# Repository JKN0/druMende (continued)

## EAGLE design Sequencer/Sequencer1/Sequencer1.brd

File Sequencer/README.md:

# Sequencer

Sequencer is  divided to two circuit boards

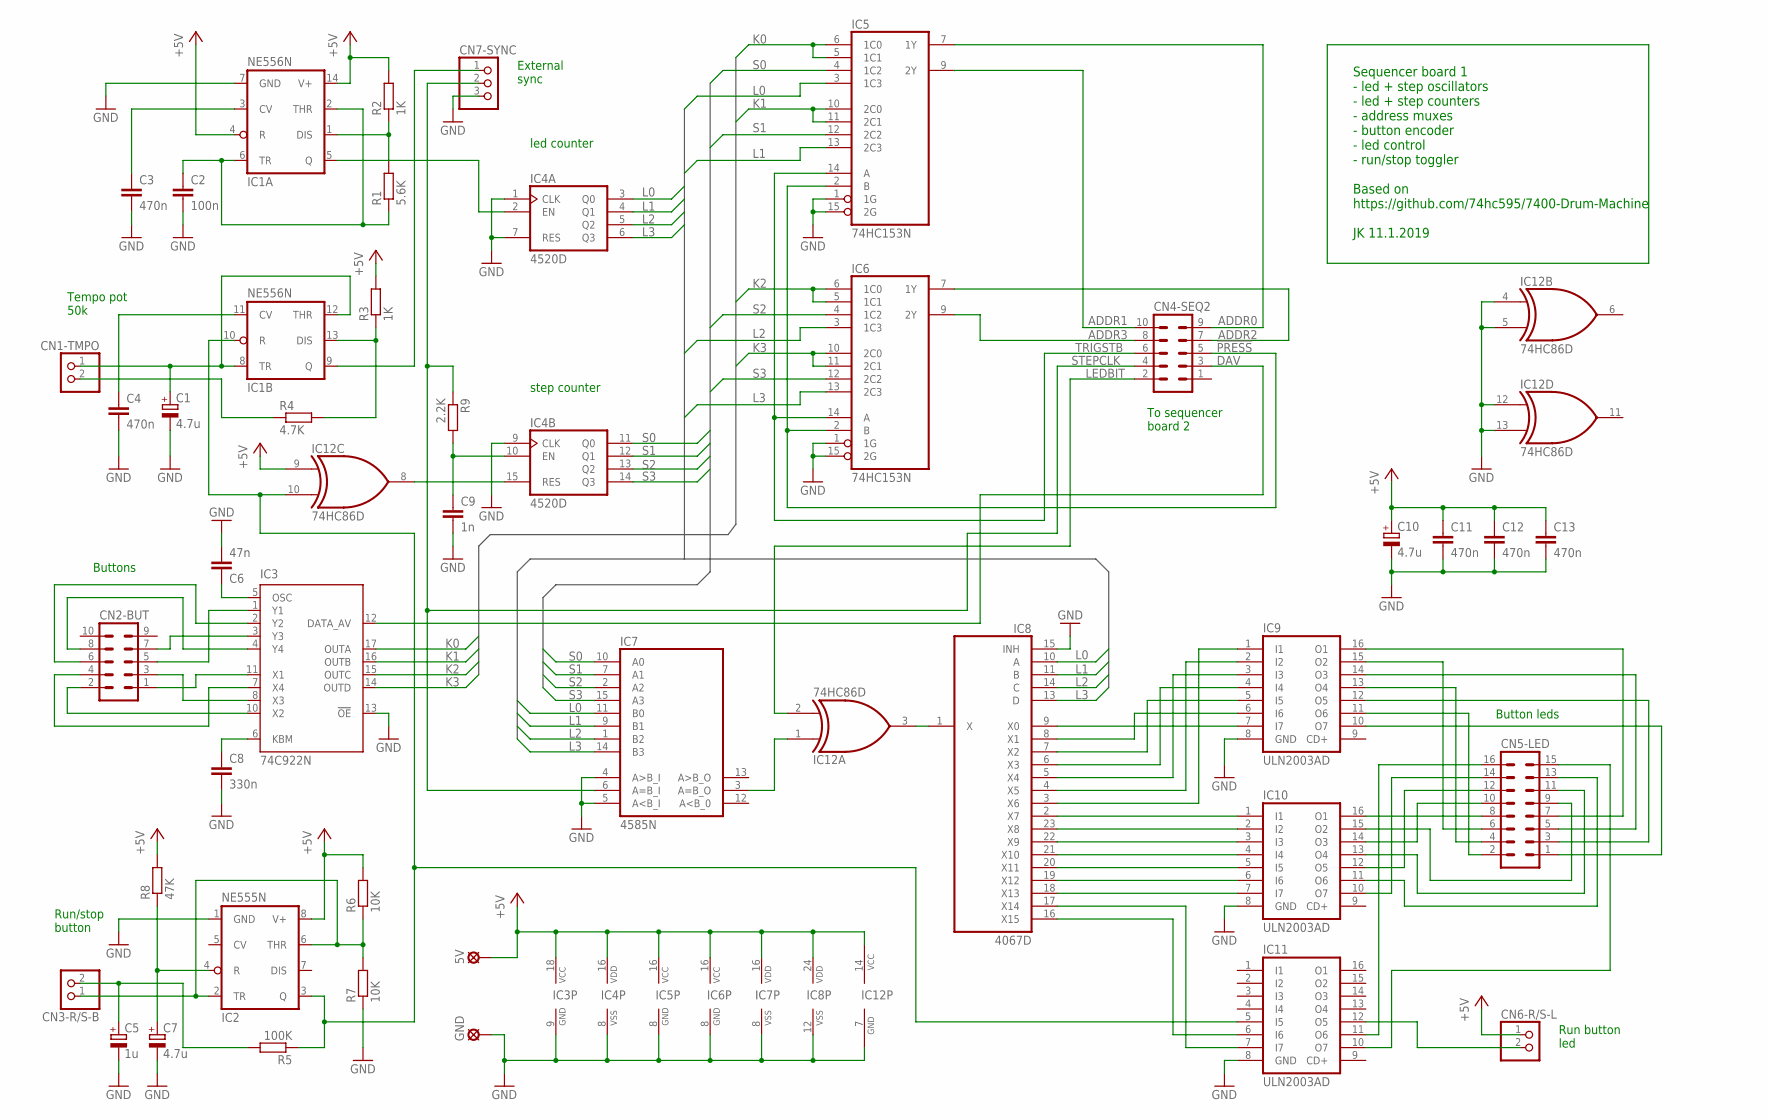
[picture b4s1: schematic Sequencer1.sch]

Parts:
5V: LSP10
C1, C7, C10: 4.7u; SMC_A
C2: 100n; C0805
C3, C4, C11, C12, C13: 470n; C0603
C5: 1u; SMC_A
C6: 47n; C0805
C8: 330n; C0805
C9: 1n; C0805
CN1-TMPO, CN3-R/S-B, CN6-R/S-L: PINHD-1X2; 1X02
CN2-BUT, CN4-SEQ2: MA05-2
CN5-LED: MA08-2
CN7-SYNC: PINHD-1X3; 1X03
GND: LSP10
IC1: NE556N; DIL14
IC2: NE555N; DIL08
IC3: 74C922N; DIL18
IC4: 4520D; SO16
IC5, IC6: 74HC153N; DIL16
IC7: 4585N; DIL16
IC8: 4067D; SO24W
IC9, IC10, IC11: ULN2003AD; SO16
IC12: 74HC86D; SO14
R1: 5.6K; R0805
R2, R3: 1K; R0805
R4: 4.7K; R0805
R5: 100K; R0805
R6, R7: 10K; R0805
R8: 47K; R0805
R9: 2.2K; R0805

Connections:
!PRESS: CN4-SEQ2.5, IC5.2 (B), IC6.2 (B)
!RUN: IC4.15 (RES), IC12.8 (O)
+5V: 5V.MP, C10.+, C11.1, C12.1, C13.1, CN6-R/S-L.1, IC1.4 (R), IC1.14 (V+), IC2.8 (V+), IC3.18 (VCC), IC4.16 (VDD), IC5.16 (VCC), IC6.16 (VCC), IC7.16 (VDD), IC8.24 (VDD), IC12.9 (I0), IC12.14 (VCC), R2.2, R3.2, R6.2, R8.2
ADDR0: CN4-SEQ2.9, IC5.7 (1Y)
ADDR1: CN4-SEQ2.10, IC5.9 (2Y)
ADDR2: CN4-SEQ2.7, IC6.7 (1Y)
ADDR3: CN4-SEQ2.8, IC6.9 (2Y)
DAV: CN4-SEQ2.3, IC3.12 (DATA_AV)
GND: C1.-, C2.2, C3.2, C4.2, C5.-, C6.2, C7.-, C8.2, C9.2, C10.-, C11.2, C12.2, C13.2, CN7-SYNC.3, GND.MP, IC1.7 (GND), IC2.1 (GND), IC3.9 (GND), IC3.13 (!OE), IC4.1 (CLK), IC4.7 (RES), IC4.8 (VSS), IC4.9 (CLK), IC5.1 (1G), IC5.8 (GND), IC5.15 (2G), IC6.1 (1G), IC6.8 (GND), IC6.15 (2G), IC7.4 (A>B_I), IC7.5 (A<B_I), IC7.8 (VSS), IC8.12 (VSS), IC8.15 (INH), IC9.8 (GND), IC10.8 (GND), IC11.8 (GND), IC12.4 (I0), IC12.5 (I1), IC12.7 (GND), IC12.12 (I0), IC12.13 (I1), R7.1
K0: IC3.17 (OUTA), IC5.5 (1C1), IC5.6 (1C0)
K1: IC3.16 (OUTB), IC5.10 (2C0), IC5.11 (2C1)
K2: IC3.15 (OUTC), IC6.5 (1C1), IC6.6 (1C0)
K3: IC3.14 (OUTD), IC6.10 (2C0), IC6.11 (2C1)
L0: IC4.3 (Q0), IC5.3 (1C3), IC7.11 (B0), IC8.10 (A)
L1: IC4.4 (Q1), IC5.13 (2C3), IC7.9 (B1), IC8.11 (B)
L2: IC4.5 (Q2), IC6.3 (1C3), IC7.1 (B2), IC8.14 (C)
L3: IC4.6 (Q3), IC6.13 (2C3), IC7.14 (B3), IC8.13 (D)
LED0: CN5-LED.1, IC9.10 (O7)
LED1: CN5-LED.2, IC9.11 (O6)
LED2: CN5-LED.3, IC9.12 (O5)
LED3: CN5-LED.4, IC9.13 (O4)
LED4: CN5-LED.5, IC9.14 (O3)
LED5: CN5-LED.6, IC9.15 (O2)
LED6: CN5-LED.7, IC9.16 (O1)
LED7: CN5-LED.8, IC10.16 (O1)
LED8: CN5-LED.9, IC10.15 (O2)
LED9: CN5-LED.10, IC10.14 (O3)
LED10: CN5-LED.11, IC10.13 (O4)
LED11: CN5-LED.12, IC10.12 (O5)
LED12: CN5-LED.13, IC10.11 (O6)
LED13: CN5-LED.14, IC10.10 (O7)
LED14: CN5-LED.15, IC11.10 (O7)
LED15: CN5-LED.16, IC11.11 (O6)
LEDBIT: CN4-SEQ2.2, IC12.2 (I1)
LEDCLK: IC1.5 (Q), IC4.2 (EN)
unnamed: C3.1, IC1.3 (CV)
unnamed: C2.1, IC1.2 (THR), IC1.6 (TR), R1.1
unnamed: C1.+, CN1-TMPO.1, IC1.8 (TR), IC1.12 (THR)
unnamed: IC1.1 (DIS), R1.2, R2.1
unnamed: C4.1, IC1.11 (CV)
unnamed: CN1-TMPO.2, R4.1
unnamed: IC1.13 (DIS), R3.1, R4.2
unnamed: CN3-R/S-B.1, IC2.2 (TR), IC2.6 (THR), R6.1, R7.2
unnamed: C8.1, IC3.6 (KBM)
unnamed: C6.1, IC3.5 (OSC)
unnamed: C5.+, CN3-R/S-B.2, R5.2
unnamed: IC8.9 (X0), IC9.7 (I7)
unnamed: IC8.7 (X2), IC9.5 (I5)
unnamed: C7.+, IC2.4 (R), R8.1
unnamed: IC8.6 (X3), IC9.4 (I4)
unnamed: IC8.5 (X4), IC9.3 (I3)
unnamed: IC8.4 (X5), IC9.2 (I2)
unnamed: C9.1, IC4.10 (EN), R9.2
unnamed: IC8.3 (X6), IC9.1 (I1)
unnamed: IC8.2 (X7), IC10.1 (I1)
unnamed: IC8.23 (X8), IC10.2 (I2)
unnamed: IC8.22 (X9), IC10.3 (I3)
unnamed: IC8.21 (X10), IC10.4 (I4)
unnamed: IC8.20 (X11), IC10.5 (I5)
unnamed: IC8.19 (X12), IC10.6 (I6)
unnamed: IC8.18 (X13), IC10.7 (I7)
unnamed: IC8.17 (X14), IC11.7 (I7)
unnamed: IC8.16 (X15), IC11.6 (I6)
unnamed: IC8.1 (X), IC12.3 (O)
unnamed: IC7.3 (A=B_O), IC12.1 (I0)
unnamed: IC8.8 (X1), IC9.6 (I6)
RUN: IC1.10 (R), IC2.3 (Q), IC11.5 (I5), IC12.10 (I1), R5.1
RUNLED: CN6-R/S-L.2, IC11.12 (O5)
S0: IC4.11 (Q0), IC5.4 (1C2), IC7.10 (A0)
S1: IC4.12 (Q1), IC5.12 (2C2), IC7.7 (A1)
S2: IC4.13 (Q2), IC6.4 (1C2), IC7.2 (A2)
S3: IC4.14 (Q3), IC6.12 (2C2), IC7.15 (A3)
STEPCLK: CN4-SEQ2.4, CN7-SYNC.2, IC7.6 (A=B_I), R9.1
STEPCLK_OUT: CN7-SYNC.1, IC1.9 (Q)
TRIGSTB: CN4-SEQ2.6, IC5.14 (A), IC6.14 (A)
X1: CN2-BUT.1, IC3.11 (X1)
X2: CN2-BUT.2, IC3.10 (X2)
X3: CN2-BUT.3, IC3.8 (X3)
X4: CN2-BUT.4, IC3.7 (X4)
Y1: CN2-BUT.5, IC3.1 (Y1)
Y2: CN2-BUT.6, IC3.2 (Y2)
Y3: CN2-BUT.7, IC3.3 (Y3)
Y4: CN2-BUT.8, IC3.4 (Y4)

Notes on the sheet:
Tempo pot 50k
Buttons
Run/stop button
To sequencer board 2
Button leds
Run button led
Sequencer board 1 - led + step oscillators - led + step counters - address muxes - button encoder - led control - run/stop toggler Based on https://github.com/74hc595/7400-Drum-Machine JK 11.1.2019
led counter
step counter
External sync

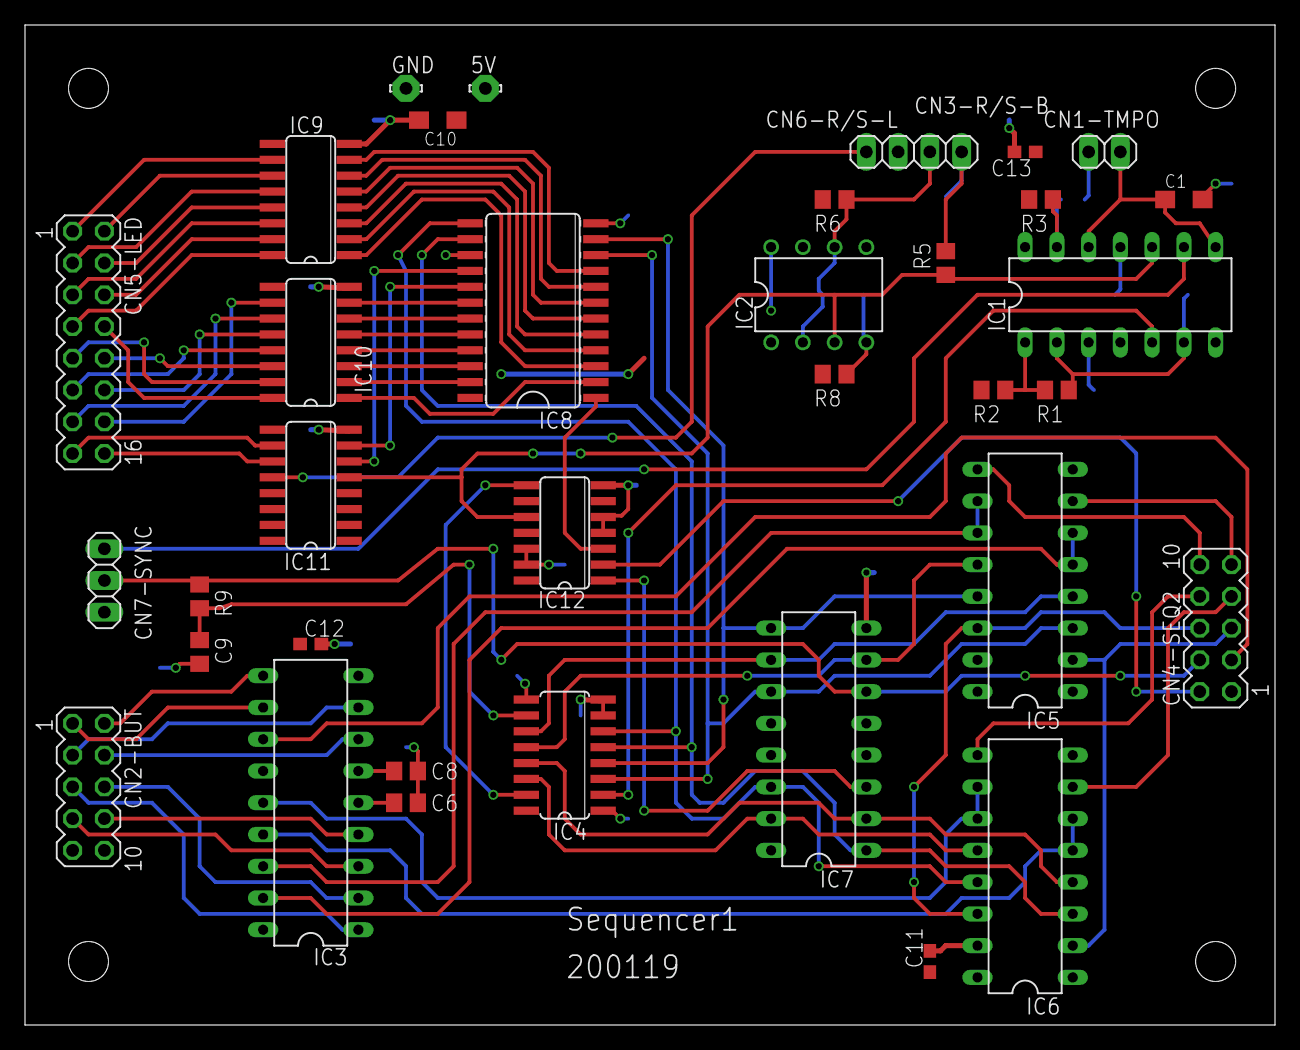
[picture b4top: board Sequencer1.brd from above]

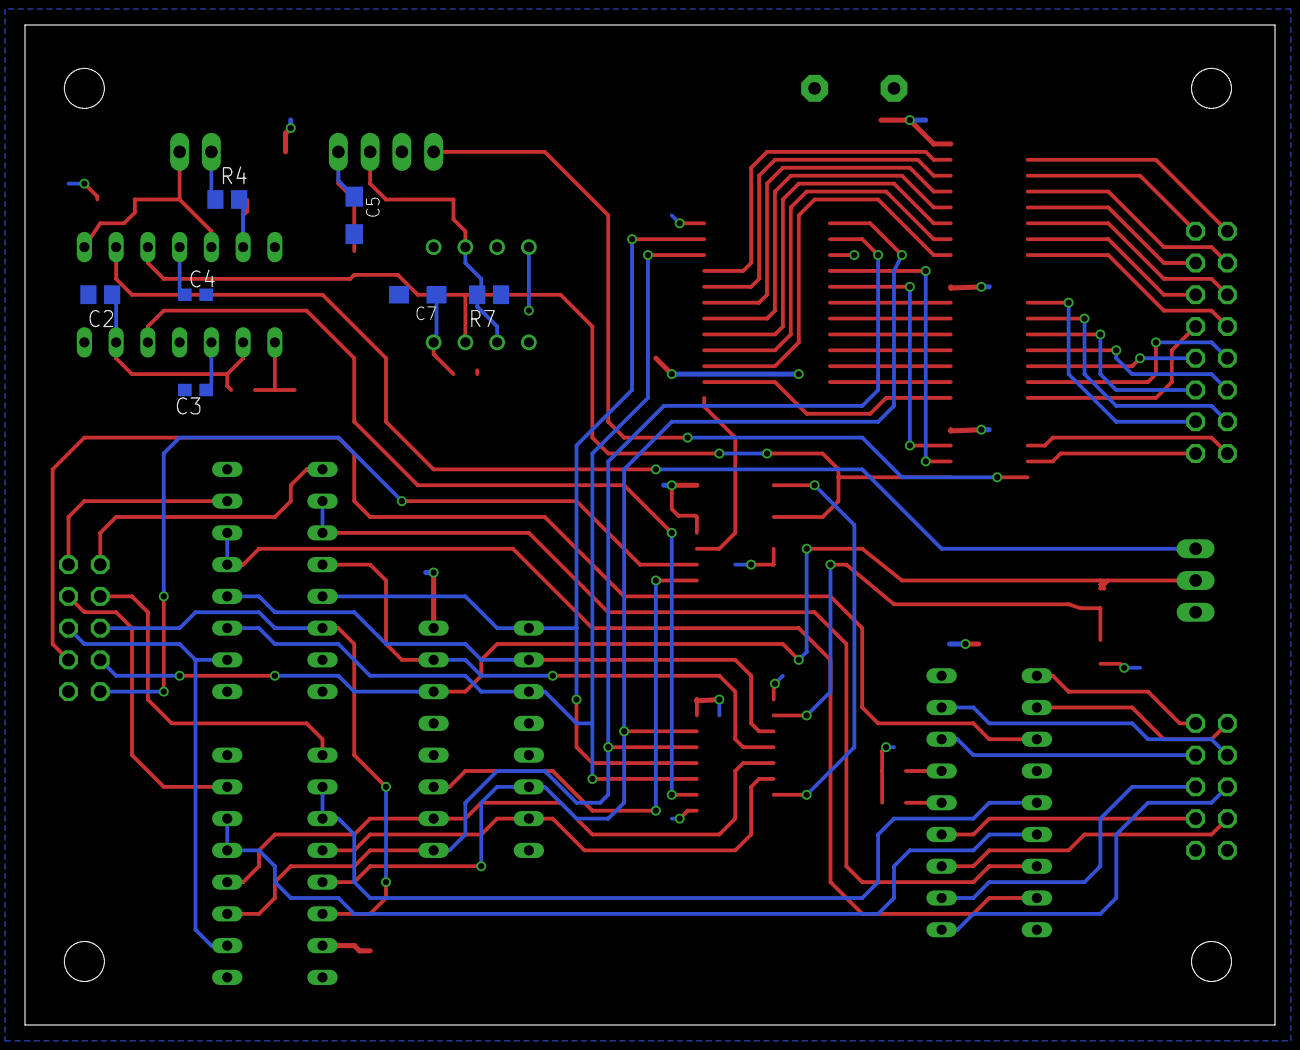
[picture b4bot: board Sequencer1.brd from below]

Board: 2 copper layers, 100.0 x 80.0 mm, 43 parts (7 on the bottom side), 83 nets.

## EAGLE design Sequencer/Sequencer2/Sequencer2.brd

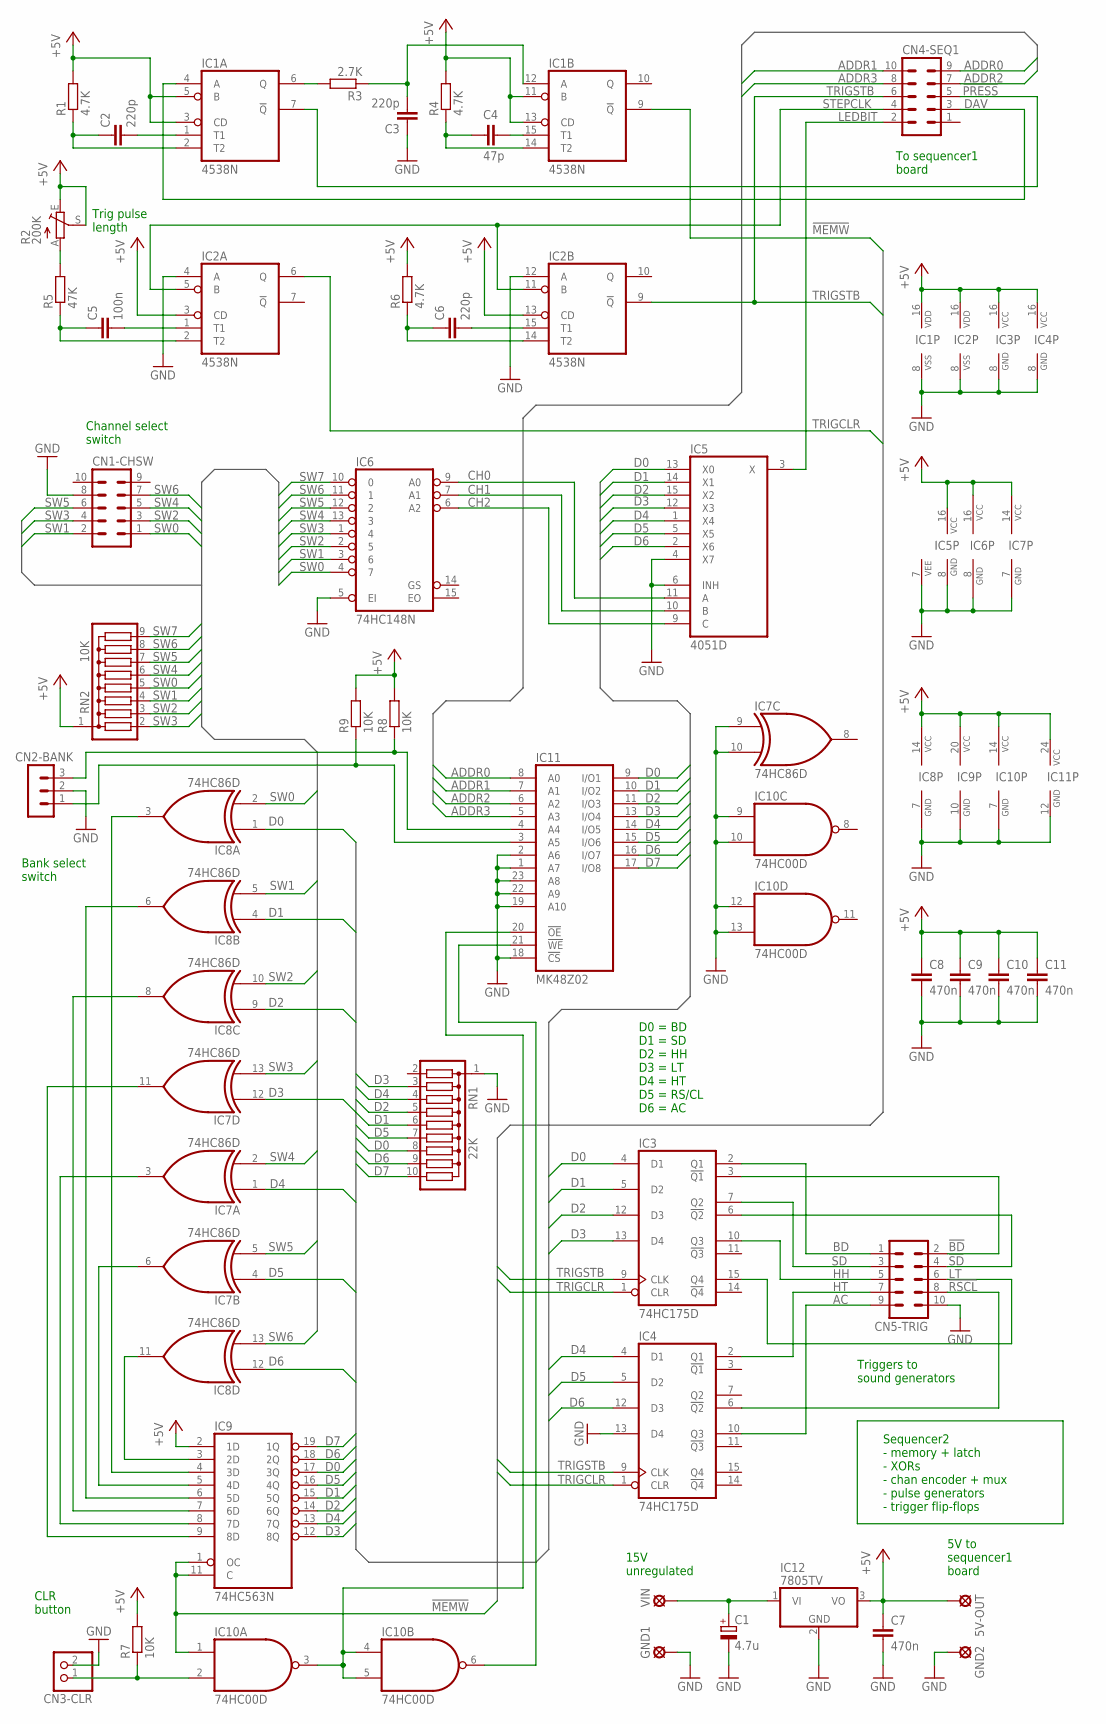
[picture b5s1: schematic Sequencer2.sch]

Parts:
5V-OUT: LSP10
C1: 4.7u; SMC_A
C2, C3, C6: 220p; C0805
C4: 47p; C0805
C5: 100n; C0805
C7, C8, C9, C10, C11: 470n; C0603
CN1-CHSW, CN4-SEQ1, CN5-TRIG: MA05-2
CN2-BANK: MA03-1
CN3-CLR: PINHD-1X2; 1X02
GND1, GND2: LSP10
IC1, IC2: 4538N; DIL16
IC3, IC4: 74HC175D; SO16
IC5: 4051D; SO16
IC6: 74HC148N; DIL16
IC7, IC8: 74HC86D; SO14
IC9: 74HC563N; DIL20
IC10: 74HC00D; SO14
IC11: MK48Z02; DIL24-6
IC12: 7805TV; TO220V
R1, R4, R6: 4.7K; R0805
R2: 200K; S63X
R3: 2.7K; R0805
R5: 47K; R0805
R7, R8, R9: 10K; R0805
RN1: 22K; SIL10
RN2: 10K; SIL9
VIN: LSP10

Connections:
!BD: CN5-TRIG.2, IC3.3 (!Q1)
!MEMW: IC1.9 (!Q), IC9.1 (OC), IC9.11 (C), IC10.1 (I0)
!PRESS: CN4-SEQ1.5, IC1.7 (!Q)
!RSCL: CN5-TRIG.8, IC4.6 (!Q2)
!SD: CN5-TRIG.4, IC3.6 (!Q2)
+5V: 5V-OUT.MP, C7.1, C8.1, C9.1, C10.1, C11.1, IC1.3 (CD), IC1.5 (B), IC1.11 (B), IC1.13 (CD), IC1.16 (VDD), IC2.3 (CD), IC2.13 (CD), IC2.16 (VDD), IC3.16 (VCC), IC4.16 (VCC), IC5.16 (VCC), IC6.16 (VCC), IC7.14 (VCC), IC8.14 (VCC), IC9.2 (1D), IC9.20 (VCC), IC10.14 (VCC), IC11.24 (VCC), IC12.3 (VO), R1.2, R2.E, R2.S, R4.2, R6.2, R7.2, R8.2, R9.2, RN2.1
AC: CN5-TRIG.9, IC4.10 (Q3)
ADDR0: CN4-SEQ1.9, IC11.8 (A0)
ADDR1: CN4-SEQ1.10, IC11.7 (A1)
ADDR2: CN4-SEQ1.7, IC11.6 (A2)
ADDR3: CN4-SEQ1.8, IC11.5 (A3)
BD: CN5-TRIG.1, IC3.2 (Q1)
CH0: IC5.11 (A), IC6.9 (A0)
CH1: IC5.10 (B), IC6.7 (A1)
CH2: IC5.9 (C), IC6.6 (A2)
D0: IC3.4 (D1), IC5.13 (X0), IC8.1 (I0), IC9.17 (3Q), IC11.9 (I/O1), RN1.8
D1: IC3.5 (D2), IC5.14 (X1), IC8.4 (I0), IC9.15 (5Q), IC11.10 (I/O2), RN1.6
D2: IC3.12 (D3), IC5.15 (X2), IC8.9 (I0), IC9.14 (6Q), IC11.11 (I/O3), RN1.5
D3: IC3.13 (D4), IC5.12 (X3), IC7.12 (I0), IC9.12 (8Q), IC11.13 (I/O4), RN1.3
D4: IC4.4 (D1), IC5.1 (X4), IC7.1 (I0), IC9.13 (7Q), IC11.14 (I/O5), RN1.4
D5: IC4.5 (D2), IC5.5 (X5), IC7.4 (I0), IC9.16 (4Q), IC11.15 (I/O6), RN1.7
D6: IC4.12 (D3), IC5.2 (X6), IC8.12 (I0), IC9.18 (2Q), IC11.16 (I/O7), RN1.9
D7: IC9.19 (1Q), IC11.17 (I/O8), RN1.10
DAV: CN4-SEQ1.3, IC1.4 (A)
GND: C1.-, C3.1, C7.2, C8.2, C9.2, C10.2, C11.2, CN1-CHSW.8, CN2-BANK.2, CN3-CLR.2, CN5-TRIG.10, GND1.MP, GND2.MP, IC1.8 (VSS), IC2.4 (A), IC2.8 (VSS), IC2.12 (A), IC3.8 (GND), IC4.8 (GND), IC4.13 (D4), IC5.4 (X7), IC5.6 (INH), IC5.7 (VEE), IC5.8 (GND), IC6.5 (EI), IC6.8 (GND), IC7.7 (GND), IC7.9 (I0), IC7.10 (I1), IC8.7 (GND), IC9.10 (GND), IC10.7 (GND), IC10.9 (I0), IC10.10 (I1), IC10.12 (I0), IC10.13 (I1), IC11.1 (A7), IC11.2 (A6), IC11.12 (GND), IC11.18 (!CS), IC11.19 (A10), IC11.22 (A9), IC11.23 (A8), IC12.2 (GND), RN1.1
HH: CN5-TRIG.5, IC3.10 (Q3)
HT: CN5-TRIG.7, IC4.2 (Q1)
LEDBIT: CN4-SEQ1.2, IC5.3 (X)
LT: CN5-TRIG.6, IC3.15 (Q4)
unnamed: C5.2, IC2.1 (T1)
unnamed: C5.1, IC2.2 (T2), R5.1
unnamed: C2.2, IC1.1 (T1)
unnamed: C2.1, IC1.2 (T2), R1.1
unnamed: IC1.6 (Q), R3.2
unnamed: C3.2, IC1.12 (A), R3.1
unnamed: C4.2, IC1.14 (T2), R4.1
unnamed: C4.1, IC1.15 (T1)
unnamed: R2.A, R5.2
unnamed: C6.2, IC2.15 (T1)
unnamed: C6.1, IC2.14 (T2), R6.1
unnamed: IC8.3 (O), IC9.4 (3D)
unnamed: IC8.6 (O), IC9.6 (5D)
unnamed: IC8.8 (O), IC9.7 (6D)
unnamed: IC7.11 (O), IC9.9 (8D)
unnamed: IC7.3 (O), IC9.8 (7D)
unnamed: IC7.6 (O), IC9.5 (4D)
unnamed: IC8.11 (O), IC9.3 (2D)
unnamed: CN2-BANK.1, IC11.3 (A5), R9.1
unnamed: CN3-CLR.1, IC10.2 (I1), R7.1
unnamed: C1.+, IC12.1 (VI), VIN.MP
unnamed: CN2-BANK.3, IC11.4 (A4), R8.1
unnamed: IC10.3 (O), IC10.4 (I0), IC10.5 (I1), IC11.20 (!OE)
unnamed: IC10.6 (O), IC11.21 (!WE)
SD: CN5-TRIG.3, IC3.7 (Q2)
STEPCLK: CN4-SEQ1.4, IC2.5 (B), IC2.11 (B)
SW0: CN1-CHSW.1, IC6.4 (7), IC8.2 (I1), RN2.5
SW1: CN1-CHSW.2, IC6.3 (6), IC8.5 (I1), RN2.4
SW2: CN1-CHSW.3, IC6.2 (5), IC8.10 (I1), RN2.3
SW3: CN1-CHSW.4, IC6.1 (4), IC7.13 (I1), RN2.2
SW4: CN1-CHSW.5, IC6.13 (3), IC7.2 (I1), RN2.6
SW5: CN1-CHSW.6, IC6.12 (2), IC7.5 (I1), RN2.7
SW6: CN1-CHSW.7, IC6.11 (1), IC8.13 (I1), RN2.8
SW7: IC6.10 (0), RN2.9
TRIGCLR: IC2.6 (Q), IC3.1 (CLR), IC4.1 (CLR)
TRIGSTB: CN4-SEQ1.6, IC2.9 (!Q), IC3.9 (CLK), IC4.9 (CLK)

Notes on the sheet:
D0 = BD D1 = SD D2 = HH D3 = LT D4 = HT D5 = RS/CL D6 = AC
Trig pulse length
Channel select switch
Bank select switch
CLR button
5V to sequencer1 board
Triggers to sound generators
To sequencer1 board
15V unregulated
Sequencer2 - memory + latch - XORs - chan encoder + mux - pulse generators - trigger flip-flops

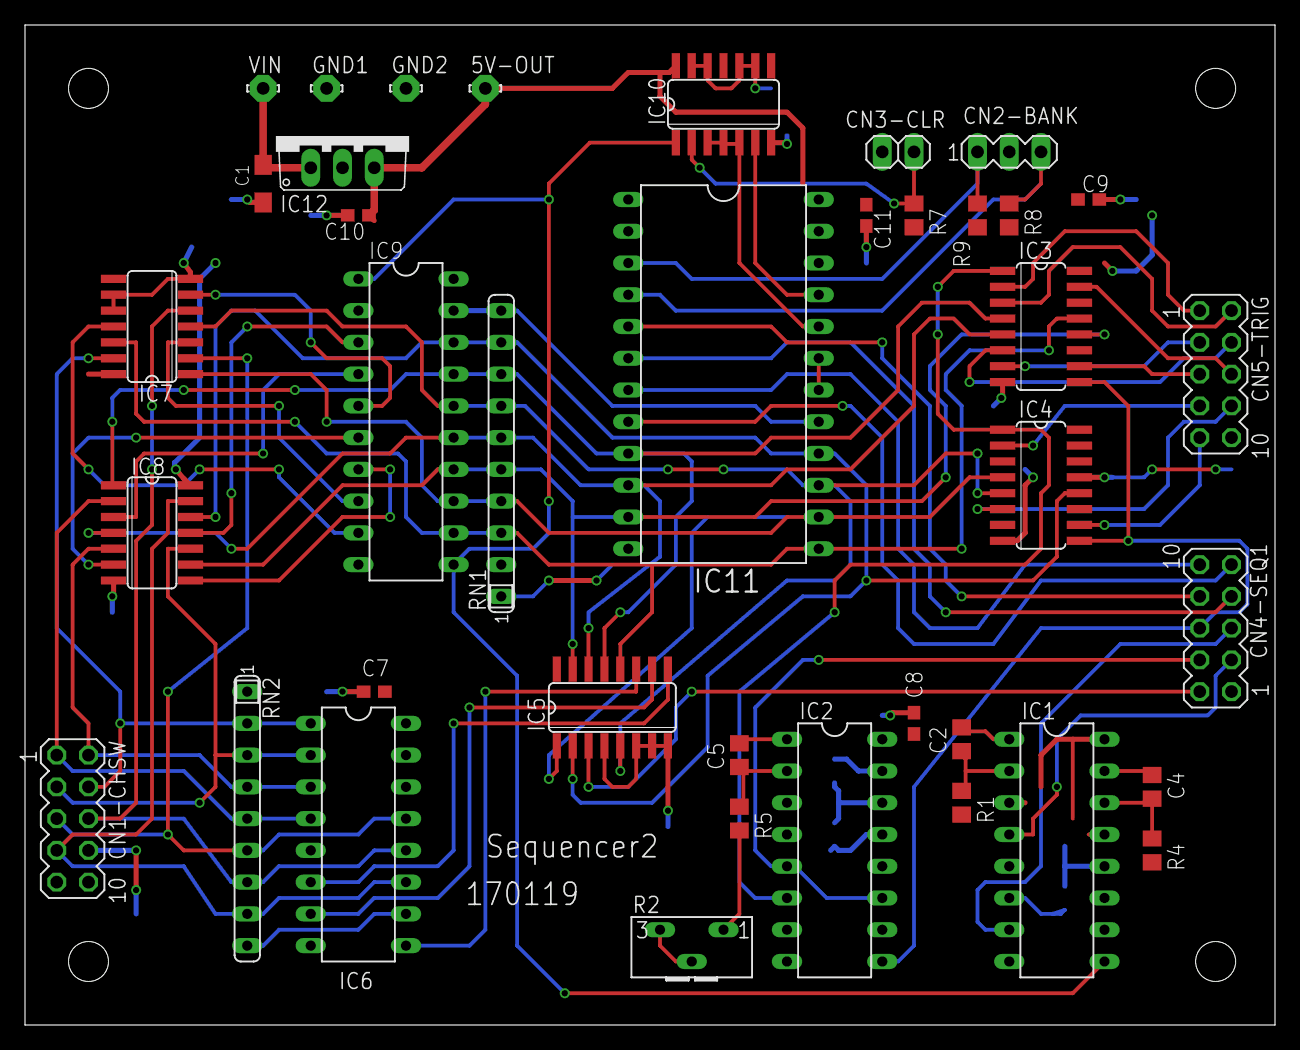
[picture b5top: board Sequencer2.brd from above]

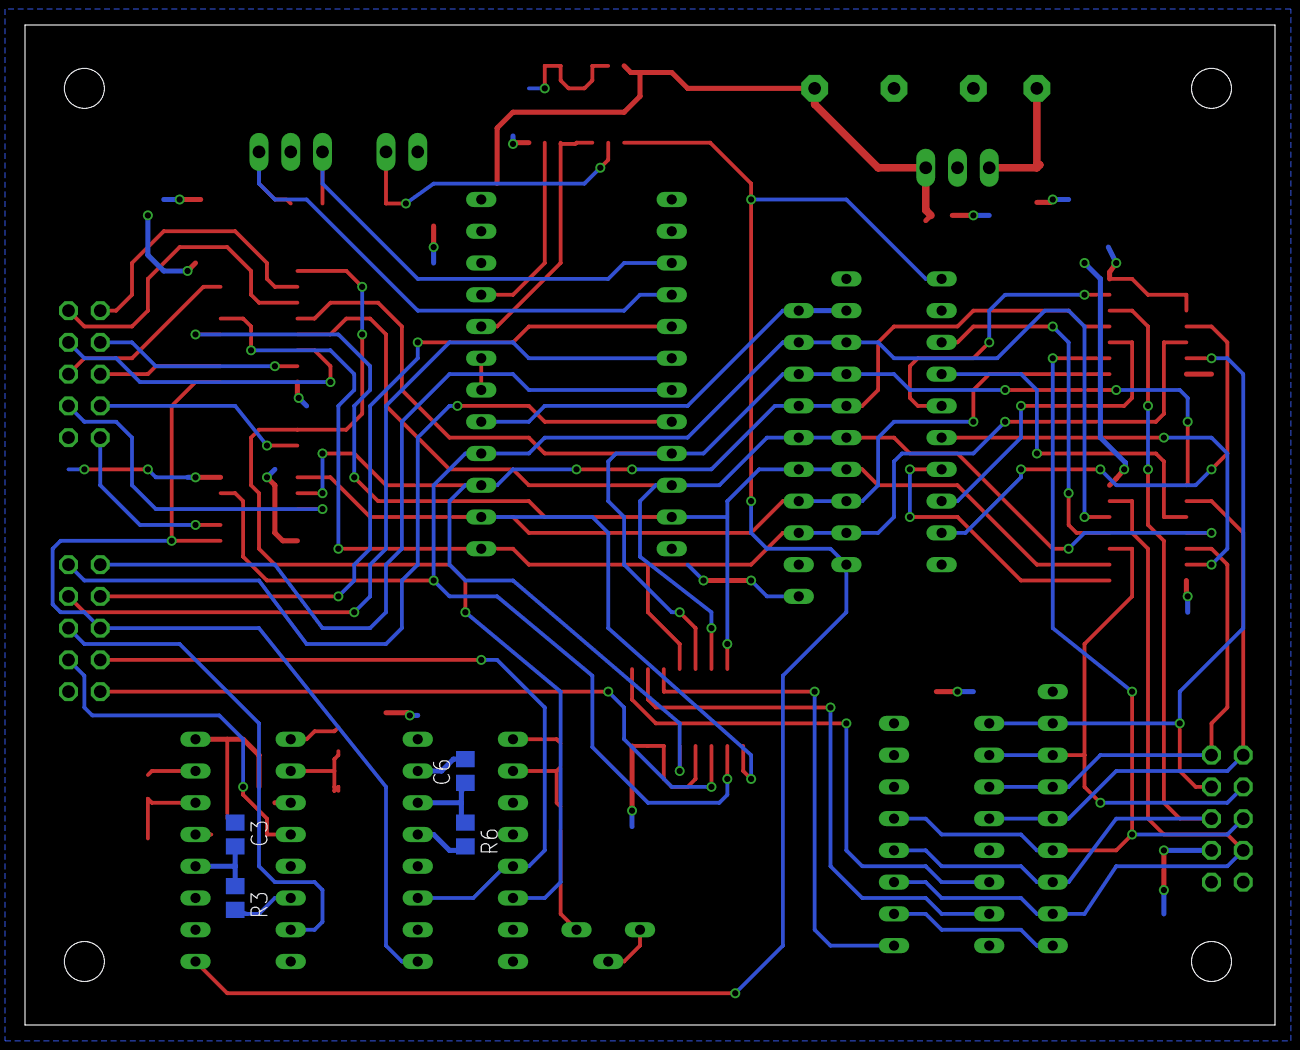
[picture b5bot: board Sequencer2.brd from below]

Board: 2 copper layers, 100.0 x 80.0 mm, 43 parts (4 on the bottom side), 65 nets.

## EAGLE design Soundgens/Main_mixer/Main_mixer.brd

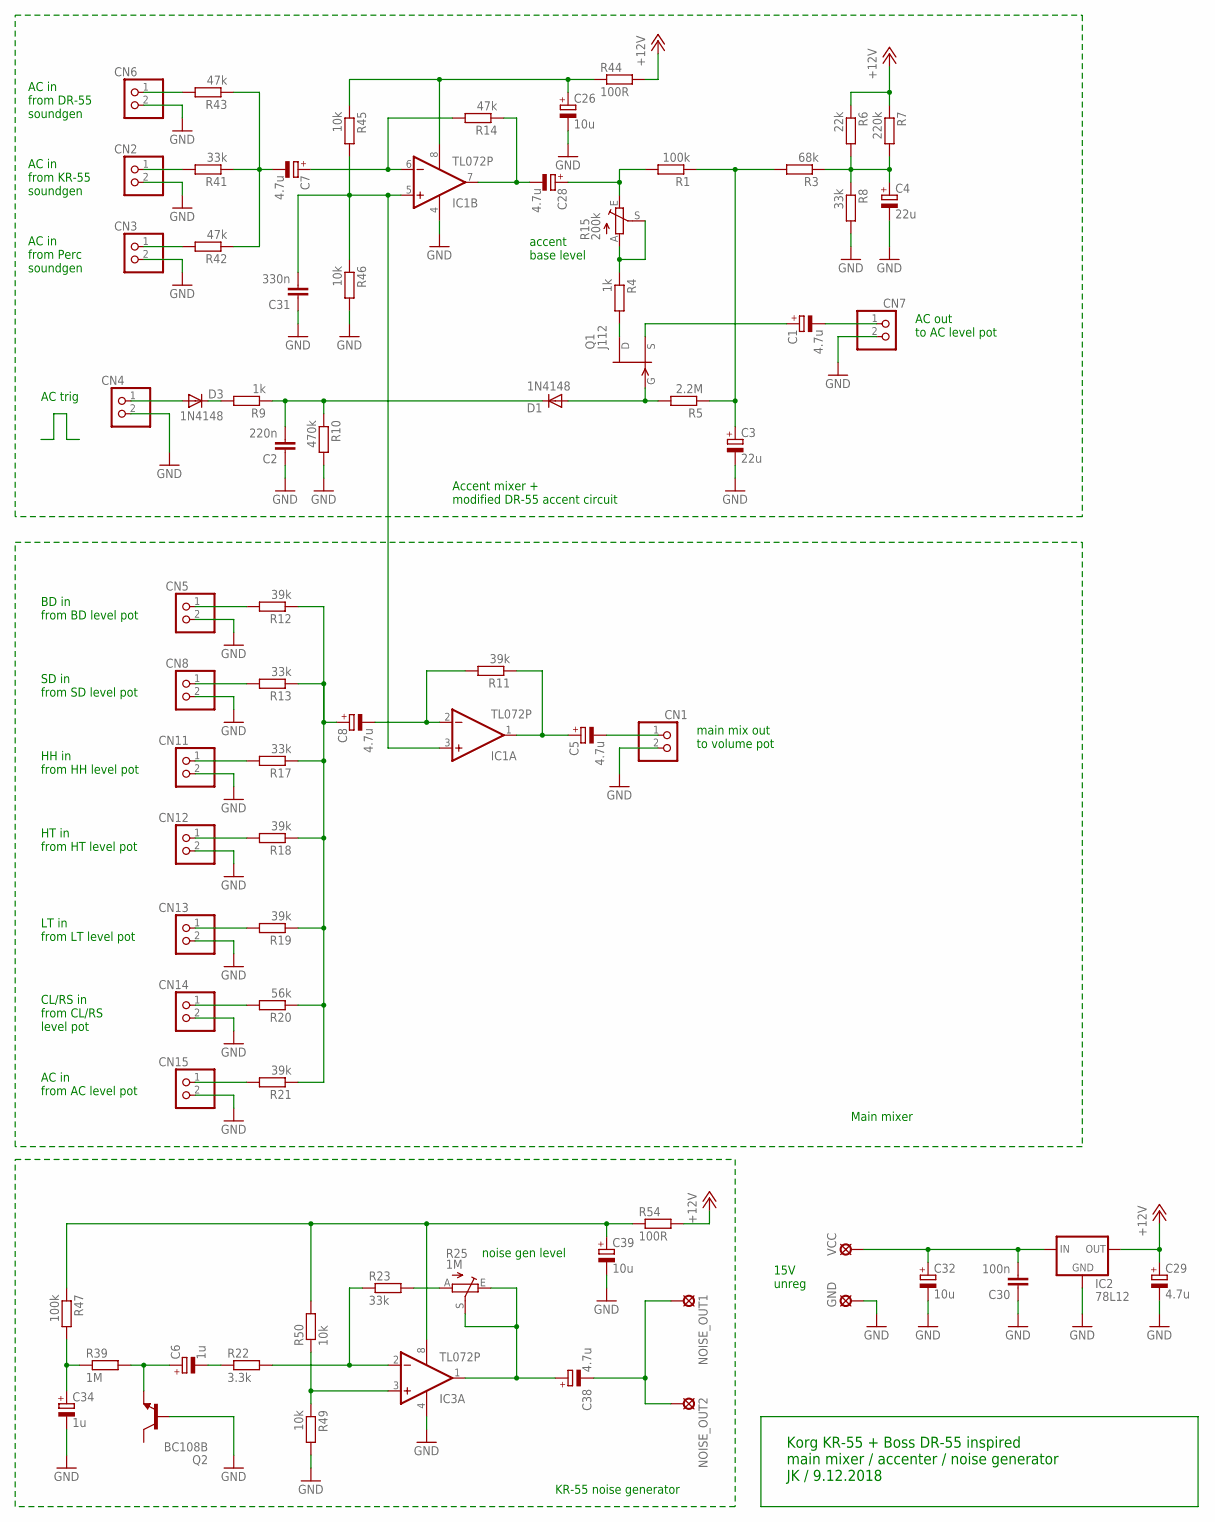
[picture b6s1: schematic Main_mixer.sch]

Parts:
C1, C5, C7, C8, C28, C29, C38: 4.7u; SMC_A
C2: 220n; C0805
C3, C4: 22u; E5-5
C6, C34: 1u; SMC_A
C26, C32, C39: 10u; E2,5-5
C30: 100n; C0805
C31: 330n; C0805
CN1, CN2, CN3, CN4, CN5, CN6, CN7, CN8, CN11, CN12, CN13, CN14, CN15: PINHD-1X2; 1X02
D1, D3: 1N4148; SOD80C
GND: LSP10
IC1, IC3: TL072P; DIL08
IC2: 78L12; 78LXX
NOISE_OUT1, NOISE_OUT2: LSP10
Q1: J112; TO92
Q2: BC108B; TO18
R1, R47: 100k; R0805
R3: 68k; R0805
R4, R9: 1k; R0805
R5: 2.2M; R0805
R6: 22k; R0805
R7: 220k; R0805
R8, R13, R17, R23, R41: 33k; R0805
R10: 470k; R0805
R11, R12, R18, R19, R21: 39k; R0805
R14, R42, R43: 47k; R0805
R15: 200k; S63X
R20: 56k; R0805
R22: 3.3k; R0805
R25: 1M; S63X
R39: 1M; R0805
R44, R54: 100R; R0805
R45, R46, R49, R50: 10k; R0805
VCC: LSP10

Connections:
+12V: C29.+, IC2.OUT, R6.1, R7.1, R44.2, R54.2
+15V: C30.2, C32.+, IC2.IN, VCC.MP
GND: C2.1, C3.-, C4.-, C26.-, C29.-, C30.1, C31.1, C32.-, C34.-, C39.-, CN1.2, CN2.2, CN3.2, CN4.2, CN5.2, CN6.2, CN7.2, CN8.2, CN11.2, CN12.2, CN13.2, CN14.2, CN15.2, GND.MP, IC1.4 (V-), IC2.GND, IC3.4 (V-), Q2.2 (B), R8.2, R10.2, R46.2, R49.2
unnamed: C31.2, IC1.3 (+IN), IC1.5 (+IN), R45.2, R46.1
unnamed: CN6.1, R43.2
unnamed: CN2.1, R41.2
unnamed: CN3.1, R42.2
unnamed: CN4.1, D3.A
unnamed: D3.C, R9.2
unnamed: C2.2, D1.C, R9.1, R10.1
unnamed: D1.A, Q1.3 (G), R5.2
unnamed: C28.+, R1.2, R15.E
unnamed: C3.+, R1.1, R3.2, R5.1
unnamed: C8.+, R12.1, R13.1, R17.1, R18.1, R19.1, R20.1, R21.1
unnamed: R4.1, R15.A, R15.S
unnamed: Q1.1 (D), R4.2
unnamed: C1.+, Q1.2 (S)
unnamed: C1.-, CN7.1
unnamed: CN5.1, R12.2
unnamed: C4.+, R3.1, R6.2, R7.2, R8.1
unnamed: CN8.1, R13.2
unnamed: CN11.1, R17.2
unnamed: CN12.1, R18.2
unnamed: CN13.1, R19.2
unnamed: CN14.1, R20.2
unnamed: CN15.1, R21.2
unnamed: C5.+, IC1.1 (OUT), R11.1
unnamed: C5.-, CN1.1
unnamed: C7.+, IC1.6 (-IN), R14.2
unnamed: R23.2, R25.A
unnamed: C38.+, IC3.1 (OUT), R25.E, R25.S
unnamed: IC3.2 (-IN), R22.2, R23.1
unnamed: C6.-, R22.1
unnamed: C6.+, Q2.1 (E), R39.2
unnamed: C34.+, R39.1, R47.2
unnamed: C38.-, NOISE_OUT1.MP, NOISE_OUT2.MP
unnamed: C8.-, IC1.2 (-IN), R11.2
unnamed: C28.-, IC1.7 (OUT), R14.1
unnamed: C7.-, R41.1, R42.1, R43.1
unnamed: IC3.3 (+IN), R49.1, R50.1
V_BD: C39.+, IC3.8 (V+), R47.1, R50.2, R54.1
V_MX: C26.+, IC1.8 (V+), R44.1, R45.1

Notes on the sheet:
main mix out to volume pot
noise gen level
AC in from DR-55 soundgen
15V unreg
KR-55 noise generator
BD in from BD level pot
Accent mixer + modified DR-55 accent circuit
Korg KR-55 + Boss DR-55 inspired main mixer / accenter / noise generator JK / 9.12.2018
AC out to AC level pot
AC in from KR-55 soundgen
AC in from Perc soundgen
accent base level
SD in from SD level pot
HH in from HH level pot
HT in from HT level pot
LT in from LT level pot
CL/RS in from CL/RS level pot
AC in from AC level pot
Main mixer
AC trig

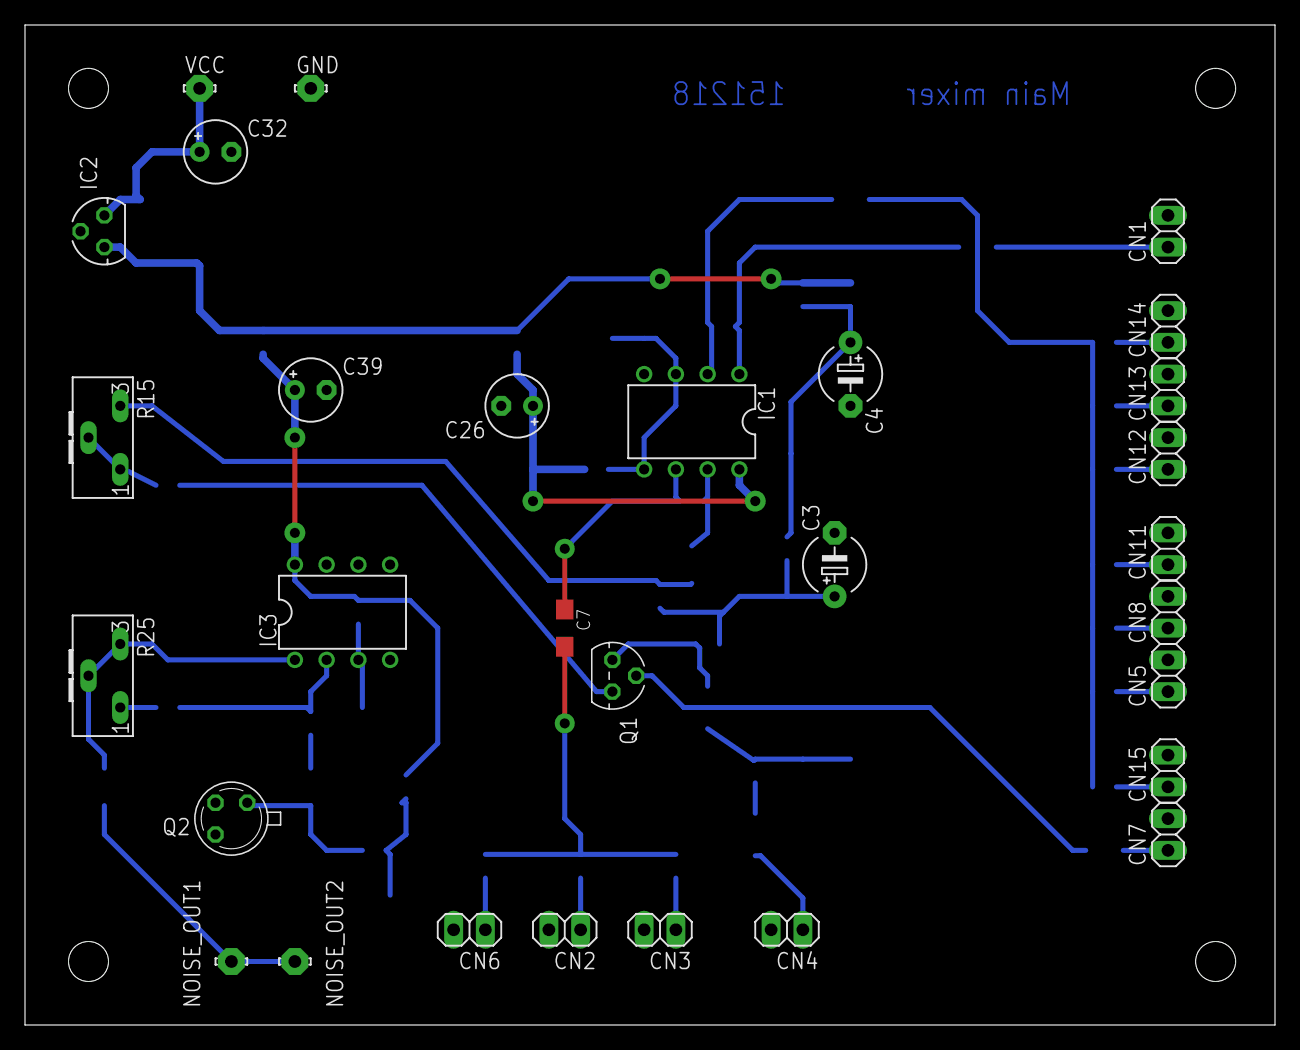
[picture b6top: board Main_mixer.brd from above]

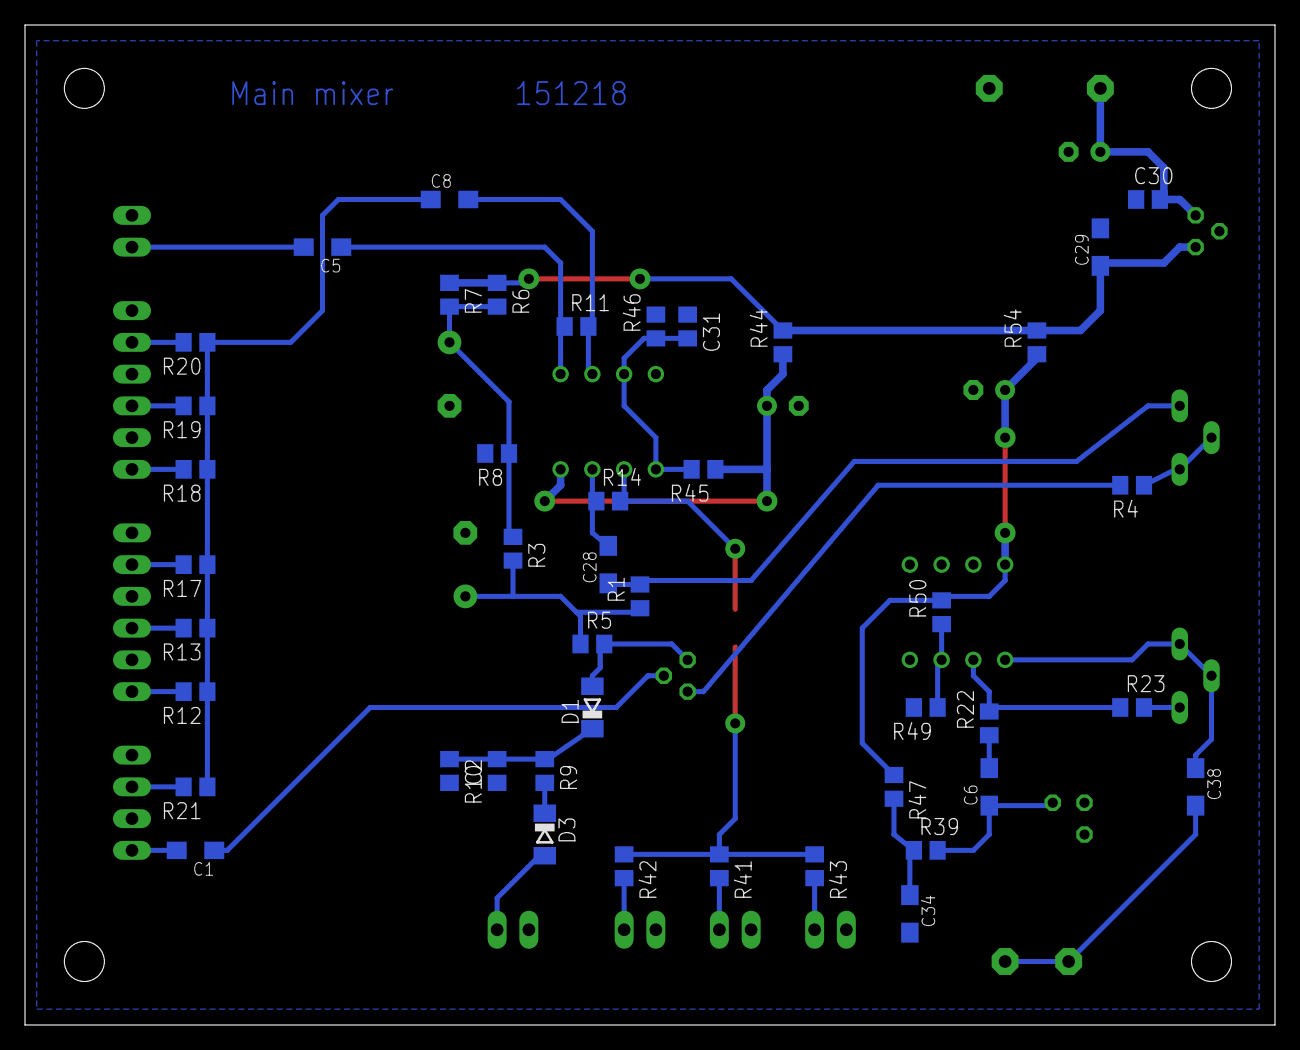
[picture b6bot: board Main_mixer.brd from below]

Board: 2 copper layers, 100.0 x 80.0 mm, 74 parts (44 on the bottom side), 42 nets.

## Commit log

2020-11-09 Analog drum machine
2020-11-09 Readme additions
